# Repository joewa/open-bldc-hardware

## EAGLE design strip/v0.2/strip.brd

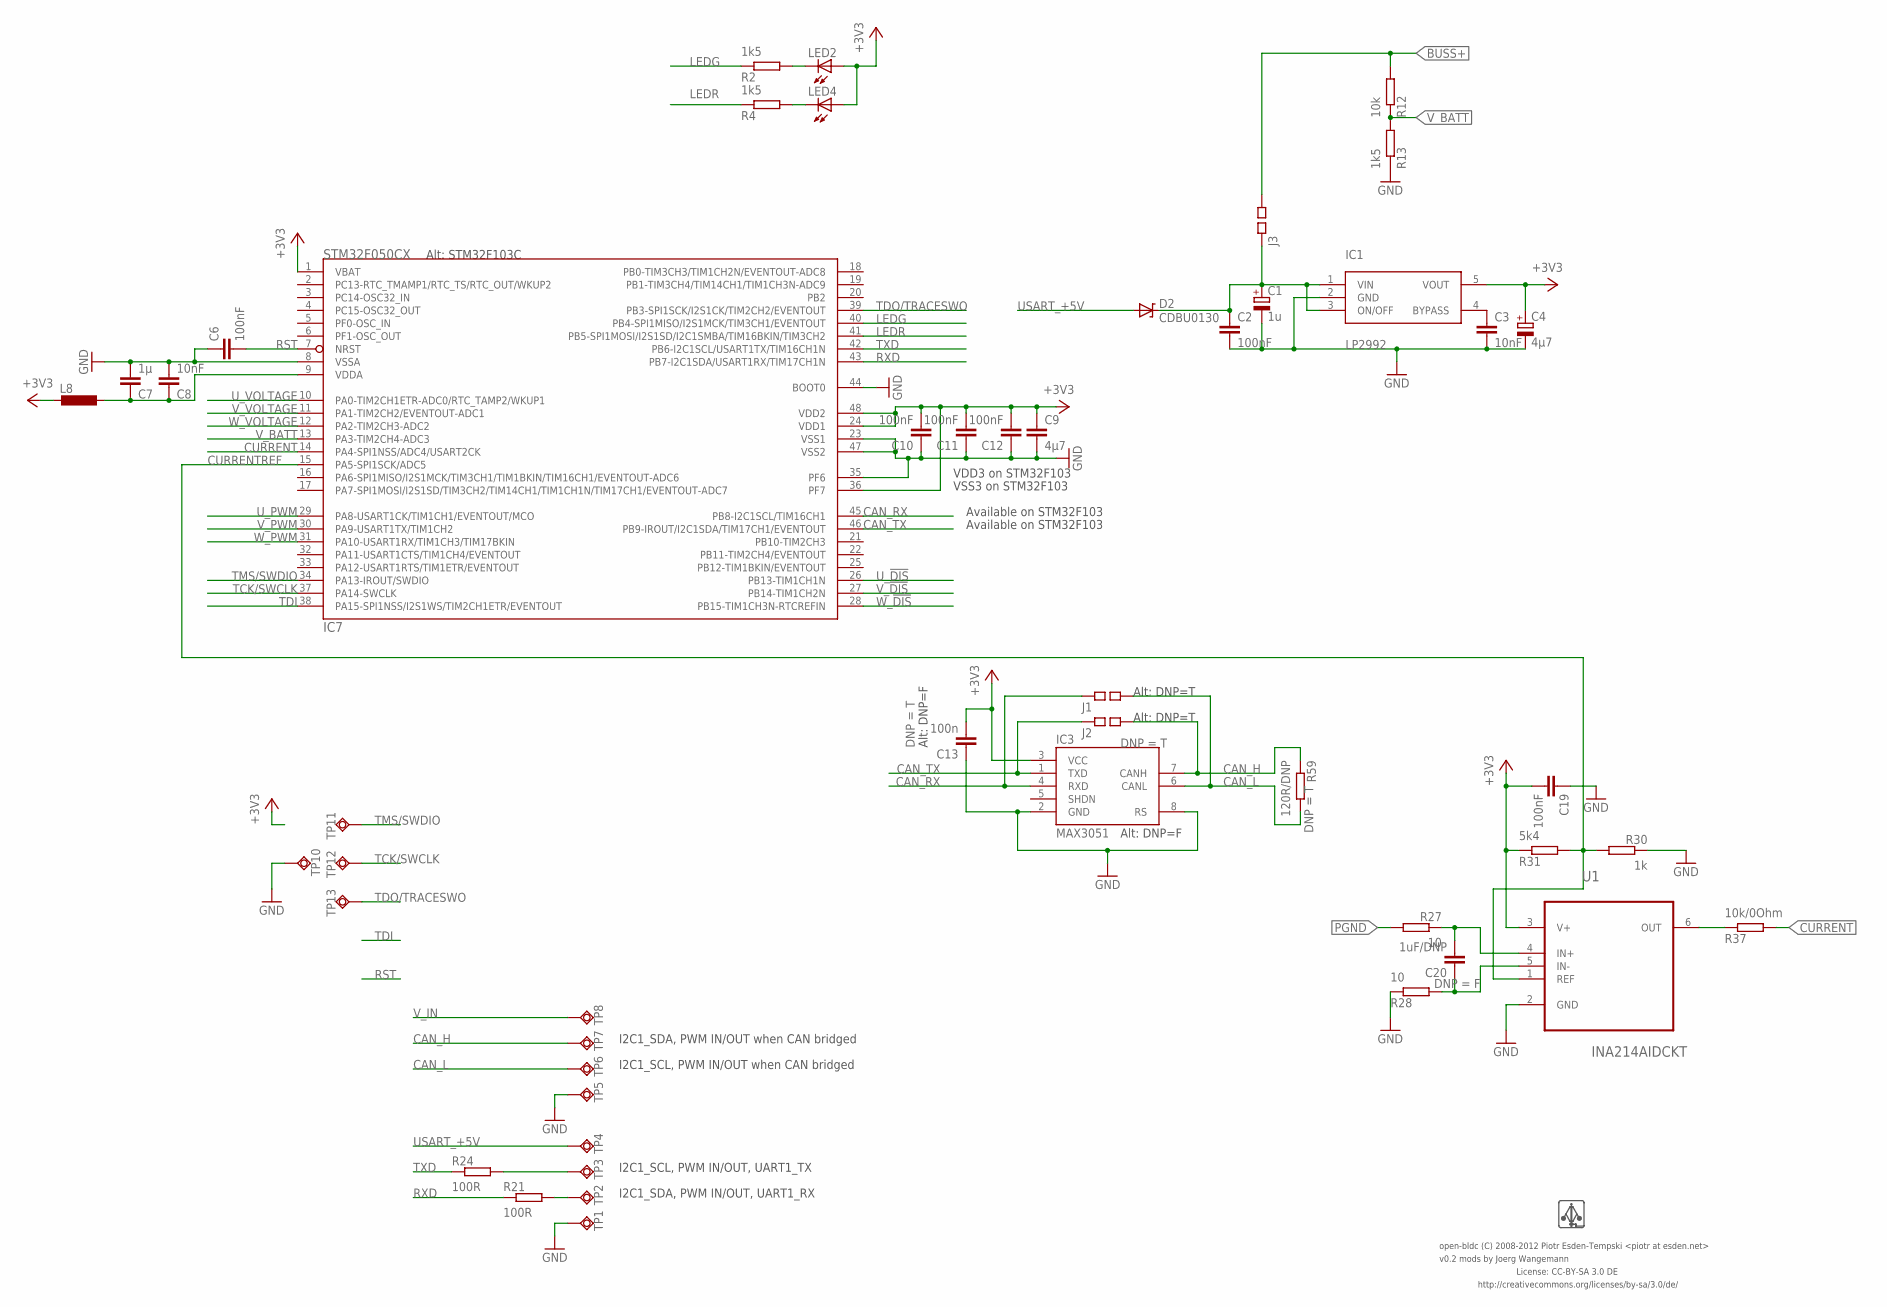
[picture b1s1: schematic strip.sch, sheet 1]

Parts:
C1: 1u; 0805-POL-CAP; PARTNO cap-cer-0805-1u-35v
C2, C6, C10, C11, C12, C19: 100nF; 0402-CAP; PARTNO cap-cer-0402-100n
C3, C8: 10nF; 0402-CAP; PARTNO cap-cer-0402-10n
C4: 4µ7; 0805-POL-CAP; PARTNO cap-cer-0805-4u7-16v
C7: 1µ; 0402-CAP; PARTNO cap-cer-0402-1u
C9: 4µ7; 0805-CAP; PARTNO cap-cer-0805-4u7
C13: 100n; 0402-CAP; PARTNO cap-cer-0402-100n
C20: 1uF/DNP; 0603-CAP; PARTNO cap-cer-0402-100n
D2: CDBU0130; 0603-DIO; PARTNO diode-0603
IC1: LP2992; SOT23-5; PARTNO vreg-sot-23-5-3v3
IC3: MAX3051; SO8; PARTNO *
IC7: STM32F050CX; LQFP48; PARTNO mcu-tqfp-32-stm32f05
J1, J2, J3: SQ_JMP-0402; 0402-SQJMP; PARTNO res-0402-0
L8: INDUCTOR-0603; 0603-IND; PARTNO ferrite-0603-600ohm
LED2: GREEN; 0402-LED; PARTNO led-0402-green
LED4: RED; 0402-LED; PARTNO led-0402-green
R2, R4, R13: 1k5; 0402-RES; PARTNO res-0402-1k5
R12: 10k; 0402-RES; PARTNO res-0402-10k
R21, R24: 100R; 0402-RES; PARTNO res-0402-100
R27: 10; 0402-RES; PARTNO res-0402-665
R28: 10; 0402-RES; PARTNO res-0402-560
R30: 1k; 0402-RES; PARTNO res-0402-1k
R31: 5k4; 0402-RES; PARTNO res-0402-5k36
R37: 10k/0Ohm; 0402-RES; PARTNO res-0402-0
R59: 120R/DNP; 0402-RES; PARTNO res-0402-60.4
TP1, TP2, TP3, TP4, TP5, TP6, TP7, TP8: TPSQTP20SQ; TP20SQ; PARTNO *
TP10, TP11, TP12, TP13: TPSQTP11SQ; TP11SQ; PARTNO *
U1: INA214AIDCKT; SOT65P210X110-6N
U$1: LOGO; LOGO_SILK_SMALL; PARTNO *

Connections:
+3V3: C4.+, C9.P$1 (1), C10.P$2 (2), C11.P$2 (2), C12.P$2 (2), C13.P$2 (2), C19.P$2 (2), IC1.5 (VOUT), IC3.3 (VCC), IC7.1 (VBAT), IC7.24 (VDD1), IC7.36 (PF7), IC7.48 (VDD2), L8.P$2 (2), LED2.A, LED4.A, R31.P$1 (1), U1.3 (V+)
BUSS+: J3.P$2 (2), R12.P$2 (2); also elsewhere on the board
CAN_H: IC3.7 (CANH), J2.P$2 (2), R59.P$1 (1), TP7.TP
CAN_L: IC3.6 (CANL), J1.P$2 (2), R59.P$2 (2), TP6.TP
CAN_RX: IC3.4 (RXD), IC7.45 (PB8-I2C1SCL/TIM16CH1), J1.P$1 (1)
CAN_TX: IC3.1 (TXD), IC7.46 (PB9-IROUT/I2C1SDA/TIM17CH1/EVENTOUT), J2.P$1 (1)
CURRENT: IC7.14 (PA4-SPI1NSS/ADC4/USART2CK), R37.P$2 (2)
CURRENTREF: IC7.15 (PA5-SPI1SCK/ADC5), R30.P$2 (2), R31.P$2 (2), U1.1 (REF)
CURRENT_RAW: R37.P$1 (1), U1.6 (OUT)
GND: C1.-, C2.P$2 (2), C3.P$2 (2), C4.-, C6.P$1 (1), C7.P$2 (2), C8.P$2 (2), C9.P$2 (2), C10.P$1 (1), C11.P$1 (1), C12.P$1 (1), C13.P$1 (1), C19.P$1 (1), IC1.2 (GND), IC3.2 (GND), IC3.8 (RS), IC7.8 (VSSA), IC7.23 (VSS1), IC7.35 (PF6), IC7.44 (BOOT0), IC7.47 (VSS2), R13.P$1 (1), R28.P$1 (1), R30.P$1 (1), TP1.TP, TP5.TP, TP10.TP, U1.2 (GND); also elsewhere on the board
INA21_INN: C20.P$1 (1), R28.P$2 (2), U1.5 (IN-)
INA21_INP: C20.P$2 (2), R27.P$1 (1), U1.4 (IN+)
LEDG: IC7.40 (PB4-SPI1MISO/I2S1MCK/TIM3CH1/EVENTOUT), R2.P$1 (1)
LEDR: IC7.41 (PB5-SPI1MOSI/I2S1SD/I2C1SMBA/TIM16BKIN/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), R4.P$1 (1)
unnamed: LED4.C, R4.P$2 (2)
unnamed: R21.P$2 (2), TP2.TP
unnamed: LED2.C, R2.P$2 (2)
unnamed: R24.P$2 (2), TP3.TP
unnamed: C3.P$1 (1), IC1.4 (BYPASS)
PGND: R27.P$2 (2); also elsewhere on the board
RST: C6.P$2 (2), IC7.7 (NRST)
RXD: IC7.43 (PB7-I2C1SDA/USART1RX/TIM17CH1N), R21.P$1 (1)
TCK/SWCLK: IC7.37 (PA14-SWCLK), TP12.TP
TDI: IC7.38 (PA15-SPI1NSS/I2S1WS/TIM2CH1ETR/EVENTOUT)
TDO/TRACESWO: IC7.39 (PB3-SPI1SCK/I2S1CK/TIM2CH2/EVENTOUT), TP13.TP
TMS/SWDIO: IC7.34 (PA13-IROUT/SWDIO), TP11.TP
TXD: IC7.42 (PB6-I2C1SCL/USART1TX/TIM16CH1N), R24.P$1 (1)
USART_+5V: D2.A, TP4.TP
U_!DIS: IC7.26 (PB13-TIM1CH1N); also elsewhere on the board
U_PWM: IC7.29 (PA8-USART1CK/TIM1CH1/EVENTOUT/MCO); also elsewhere on the board
U_VOLTAGE: IC7.10 (PA0-TIM2CH1ETR-ADC0/RTC_TAMP2/WKUP1); also elsewhere on the board
VDDA: C7.P$1 (1), C8.P$1 (1), IC7.9 (VDDA), L8.P$1 (1)
V_!DIS: IC7.27 (PB14-TIM1CH2N); also elsewhere on the board
V_BATT: IC7.13 (PA3-TIM2CH4-ADC3), R12.P$1 (1), R13.P$2 (2)
V_IN: C1.+, C2.P$1 (1), D2.C, IC1.1 (VIN), IC1.3 (ON/OFF), J3.P$1 (1), TP8.TP
V_PWM: IC7.30 (PA9-USART1TX/TIM1CH2); also elsewhere on the board
V_VOLTAGE: IC7.11 (PA1-TIM2CH2/EVENTOUT-ADC1); also elsewhere on the board
W_!DIS: IC7.28 (PB15-TIM1CH3N-RTCREFIN); also elsewhere on the board
W_PWM: IC7.31 (PA10-USART1RX/TIM1CH3/TIM17BKIN); also elsewhere on the board
W_VOLTAGE: IC7.12 (PA2-TIM2CH3-ADC2); also elsewhere on the board

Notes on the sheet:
License: CC-BY-SA 3.0 DE
http://creativecommons.org/licenses/by-sa/3.0/de/
open-bldc (C) 2008-2012 Piotr Esden-Tempski <piotr at esden.net>
VDD3 on STM32F103
VSS3 on STM32F103
Available on STM32F103
Alt: STM32F103C
Alt: DNP=T
Alt: DNP=F
I2C1_SDA, PWM IN/OUT when CAN bridged
I2C1_SCL, PWM IN/OUT when CAN bridged
I2C1_SCL, PWM IN/OUT, UART1_TX
I2C1_SDA, PWM IN/OUT, UART1_RX
v0.2 mods by Joerg Wangemann

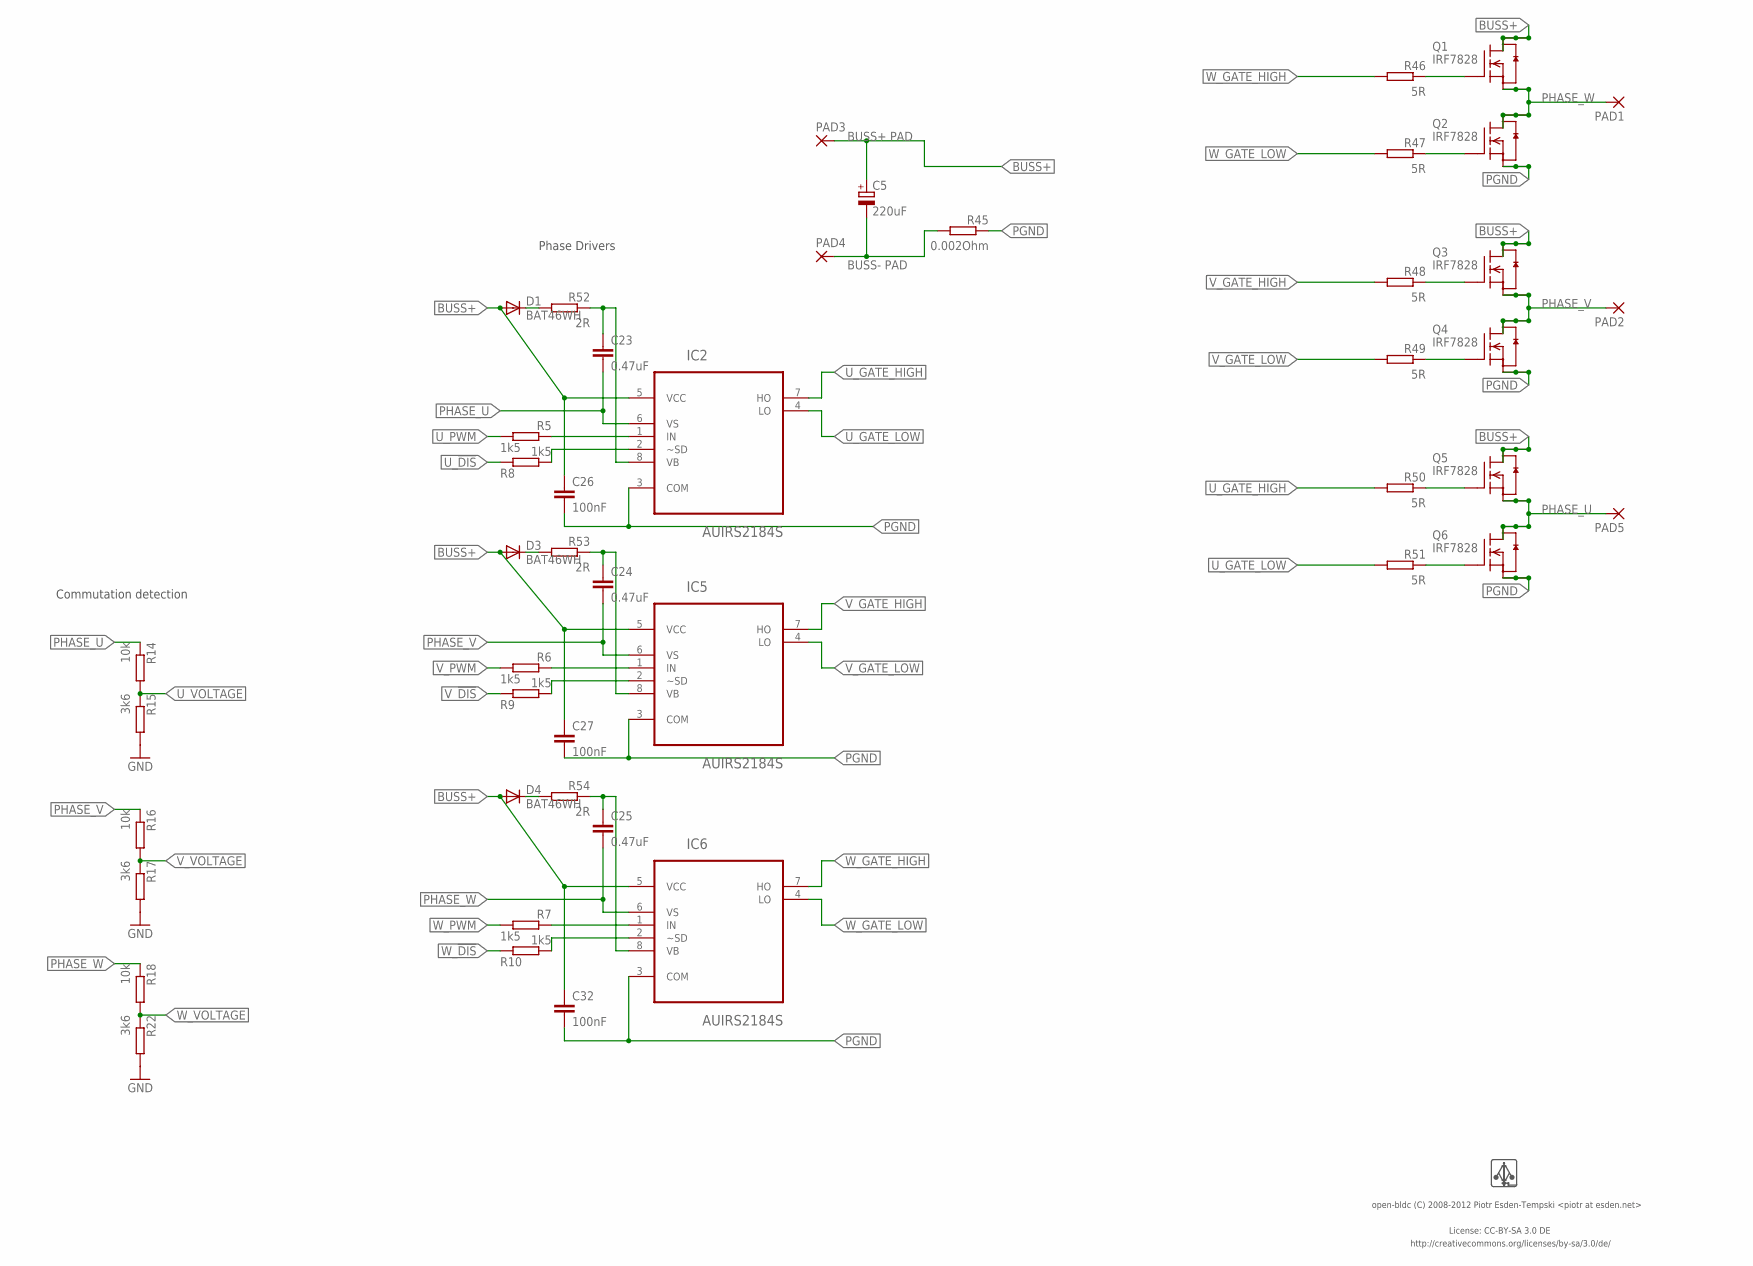
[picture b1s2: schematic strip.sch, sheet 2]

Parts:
C5: 220uF; 7343/D; PARTNO cap-tan-D-220u-16v
C23, C24, C25: 0.47uF; 0603-CAP; PARTNO cap-tan-0603-1u
C26, C27, C32: 100nF; 0603-CAP; PARTNO cap-cer-0402-100n
D1, D3, D4: BAT46WH; SOD-123-DIO; PARTNO *
IC2, IC5, IC6: AUIRS2184S; SOIC127P600X175-8N; PARTNO ic-so8-mosfet-driver-buck
PAD1, PAD2, PAD3, PAD4, PAD5: SMD5; SMD2,54-5,08; PARTNO *
Q1, Q2, Q3, Q4, Q5, Q6: IRF7828; SO8; PARTNO ic-so8-mosfet-n-ch-30v-15a
R5, R6, R7, R8, R9, R10: 1k5; 0402-RES; PARTNO res-0402-1k5
R14, R16, R18: 10k; 0402-RES; PARTNO res-0402-10k
R15, R17, R22: 3k6; 0402-RES; PARTNO *
R45: 0.002Ohm; 1206-RES; PARTNO res-1206-0005
R46, R47, R48, R49, R50, R51: 5R; 0603-RES; PARTNO res-0402-10
R52, R53, R54: 2R; 0402-RES; PARTNO res-0402-10
U$2: LOGO; LOGO_SILK_SMALL; PARTNO *

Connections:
BUSS+: C5.+, C26.P$1 (1), C27.P$1 (1), C32.P$1 (1), D1.A, D3.A, D4.A, IC2.5 (VCC), IC5.5 (VCC), IC6.5 (VCC), PAD3.1, Q1.5 (D1), Q1.6 (D2), Q1.7 (D3), Q1.8 (D4), Q3.5 (D1), Q3.6 (D2), Q3.7 (D3), Q3.8 (D4), Q5.5 (D1), Q5.6 (D2), Q5.7 (D3), Q5.8 (D4); also elsewhere on the board
GND: C5.-, PAD4.1, R15.P$2 (2), R17.P$2 (2), R22.P$2 (2), R45.P$2 (2); also elsewhere on the board
unnamed: D1.C, R52.P$2 (2)
unnamed: D4.C, R54.P$2 (2)
unnamed: D3.C, R53.P$2 (2)
PGND: C26.P$2 (2), C27.P$2 (2), C32.P$2 (2), IC2.3 (COM), IC5.3 (COM), IC6.3 (COM), Q2.1 (S3), Q2.2 (S2), Q2.3 (S1), Q4.1 (S3), Q4.2 (S2), Q4.3 (S1), Q6.1 (S3), Q6.2 (S2), Q6.3 (S1), R45.P$1 (1); also elsewhere on the board
PHASE_U: C23.P$2 (2), IC2.6 (VS), PAD5.1, Q5.1 (S3), Q5.2 (S2), Q5.3 (S1), Q6.5 (D1), Q6.6 (D2), Q6.7 (D3), Q6.8 (D4), R14.P$1 (1)
PHASE_V: C24.P$2 (2), IC5.6 (VS), PAD2.1, Q3.1 (S3), Q3.2 (S2), Q3.3 (S1), Q4.5 (D1), Q4.6 (D2), Q4.7 (D3), Q4.8 (D4), R16.P$1 (1)
PHASE_W: C25.P$2 (2), IC6.6 (VS), PAD1.1, Q1.1 (S3), Q1.2 (S2), Q1.3 (S1), Q2.5 (D1), Q2.6 (D2), Q2.7 (D3), Q2.8 (D4), R18.P$1 (1)
U_!DIS: R8.P$1 (1); also elsewhere on the board
U_GATE_HIGH: IC2.7 (HO), R50.P$2 (2)
U_GATE_HIGH_T: Q5.4 (G), R50.P$1 (1)
U_GATE_LOW: IC2.4 (LO), R51.P$2 (2)
U_GATE_LOW_T: Q6.4 (G), R51.P$1 (1)
U_PWM: R5.P$2 (2); also elsewhere on the board
U_PWM_IN: IC2.1 (IN), R5.P$1 (1)
U_SD: IC2.2 (~SD), R8.P$2 (2)
U_VB: C23.P$1 (1), IC2.8 (VB), R52.P$1 (1)
U_VOLTAGE: R14.P$2 (2), R15.P$1 (1); also elsewhere on the board
V_!DIS: R9.P$1 (1); also elsewhere on the board
V_GATE_HIGH: IC5.7 (HO), R48.P$2 (2)
V_GATE_HIGH_T: Q3.4 (G), R48.P$1 (1)
V_GATE_LOW: IC5.4 (LO), R49.P$2 (2)
V_GATE_LOW_T: Q4.4 (G), R49.P$1 (1)
V_PWM: R6.P$2 (2); also elsewhere on the board
V_PWM_IN: IC5.1 (IN), R6.P$1 (1)
V_SD: IC5.2 (~SD), R9.P$2 (2)
V_VB: C24.P$1 (1), IC5.8 (VB), R53.P$1 (1)
V_VOLTAGE: R16.P$2 (2), R17.P$1 (1); also elsewhere on the board
W_!DIS: R10.P$1 (1); also elsewhere on the board
W_GATE_HIGH: IC6.7 (HO), R46.P$2 (2)
W_GATE_HIGH_T: Q1.4 (G), R46.P$1 (1)
W_GATE_LOW: IC6.4 (LO), R47.P$2 (2)
W_GATE_LOW_T: Q2.4 (G), R47.P$1 (1)
W_PWM: R7.P$2 (2); also elsewhere on the board
W_PWM_IN: IC6.1 (IN), R7.P$1 (1)
W_SD: IC6.2 (~SD), R10.P$2 (2)
W_VB: C25.P$1 (1), IC6.8 (VB), R54.P$1 (1)
W_VOLTAGE: R18.P$2 (2), R22.P$1 (1); also elsewhere on the board

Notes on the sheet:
Phase Drivers
Commutation detection
BUSS+ PAD
BUSS- PAD
License: CC-BY-SA 3.0 DE
http://creativecommons.org/licenses/by-sa/3.0/de/
open-bldc (C) 2008-2012 Piotr Esden-Tempski <piotr at esden.net>

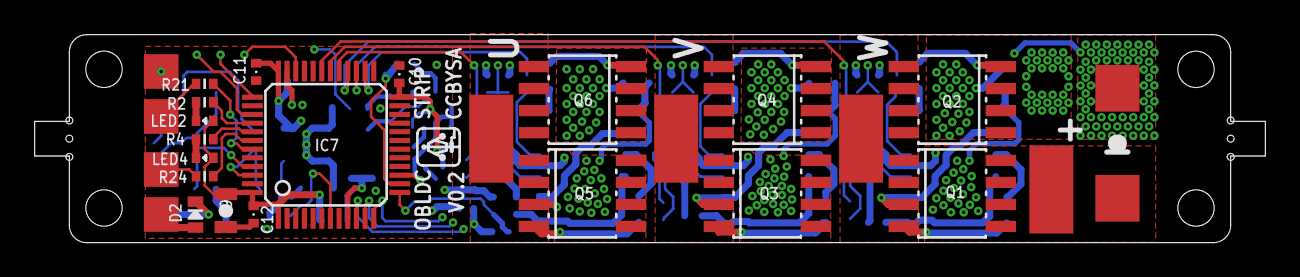
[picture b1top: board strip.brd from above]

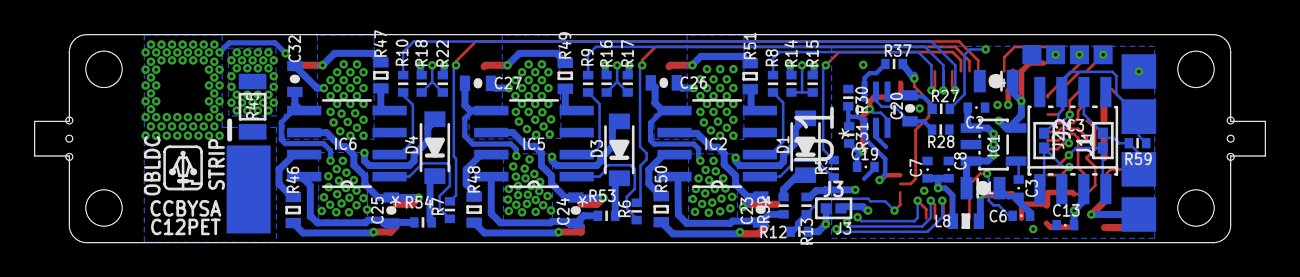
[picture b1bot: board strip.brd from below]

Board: 4 copper layers, 71.0 x 12.0 mm, 97 parts (69 on the bottom side), 66 nets.

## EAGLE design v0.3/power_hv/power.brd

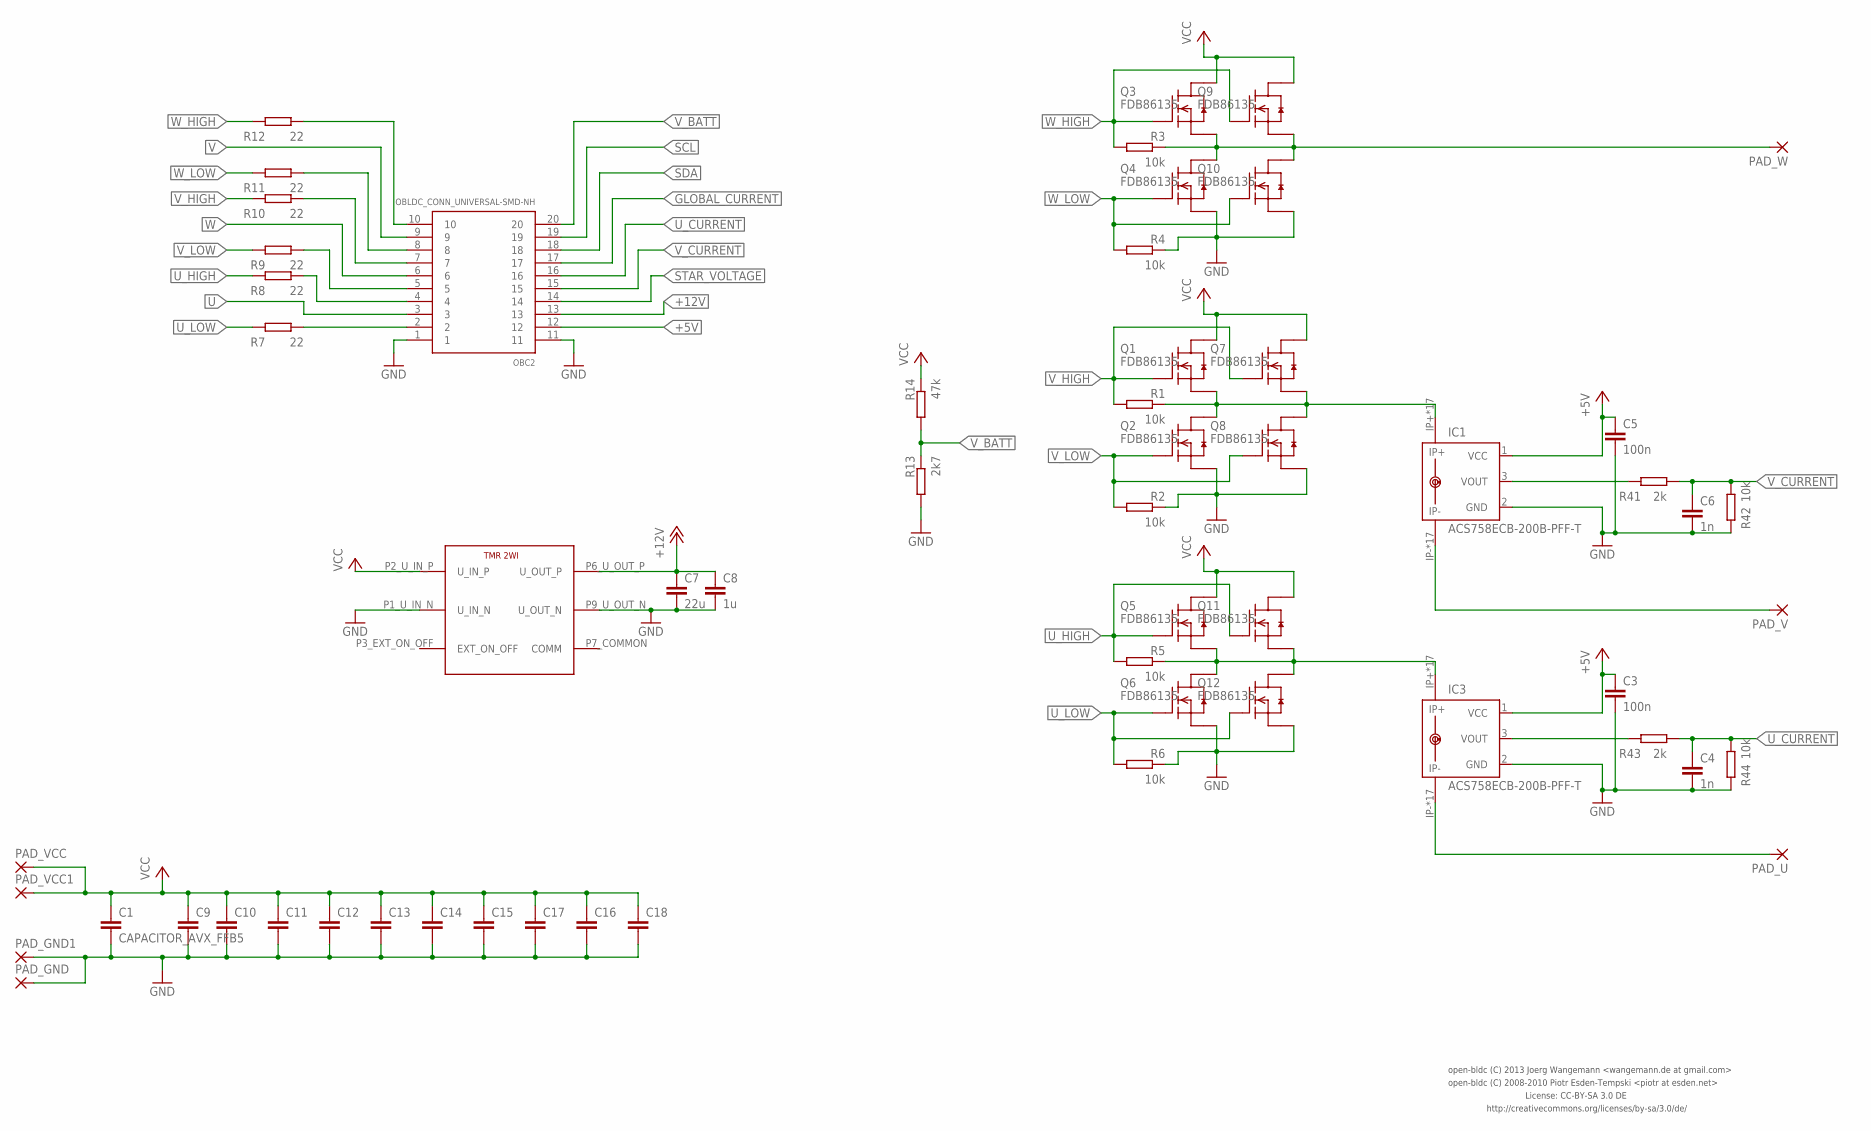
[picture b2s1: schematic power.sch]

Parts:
C1: CAPACITOR_AVX_FFB5; AVX_FFB5
C3, C5: 100n; 0603-CAP
C4, C6: 1n; 0603-CAP
C7: 22u; C2220K
C8: 1u; C1206
C9, C10, C11, C12, C13, C14, C15, C16, C17, C18: C-EUC2220K; C2220K
IC1, IC3: ACS758ECB-200B-PFF-T; CB-PFF
OBC2: OBLDC_CONN_UNIVERSAL-SMD-NH; OBLDC_CONN_SMD_NO_HOLES
PAD_GND, PAD_GND1: WIREPAD-2MM; WIREPAD_2MM
PAD_U: WIREPAD-2MM; WIREPAD_2MM
PAD_V: WIREPAD-2MM; WIREPAD_2MM
PAD_VCC, PAD_VCC1: WIREPAD-2MM; WIREPAD_2MM
PAD_W: WIREPAD-2MM; WIREPAD_2MM
Q1, Q2, Q3, Q4, Q5, Q6, Q7, Q8, Q9, Q10, Q11, Q12: FDB86135; DPAK
R1, R2, R3, R4, R5, R6: 10k; 0603-SF-RES
R7, R8, R9, R10, R11, R12: 22; 1206-RES
R13: 2k7; 1206-RES
R14: 47k; 1206-RES
R41, R43: 2k; 0603-RES
R42, R44: 10k; 0603-RES
U$2: TRACO_TMR_2WI

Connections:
+5V: C3.P$1 (1), C5.P$1 (1), IC1.1 (VCC), IC3.1 (VCC), OBC2.12
+12V: C7.1, C8.1, OBC2.13, U$2.P6_U_OUT_P (U_OUT_P)
GLOBAL_CURRENT: OBC2.17
GND: C1.P$2 (2), C3.P$2 (2), C4.P$2 (2), C5.P$2 (2), C6.P$2 (2), C7.2, C8.2, C9.2, C10.2, C11.2, C12.2, C13.2, C14.2, C15.2, C16.2, C17.2, C18.2, IC1.2 (GND), IC3.2 (GND), OBC2.1, OBC2.11, PAD_GND.1, PAD_GND1.1, Q2.3 (S), Q4.3 (S), Q6.3 (S), Q8.3 (S), Q10.3 (S), Q12.3 (S), R2.1, R4.1, R6.1, R13.P$2 (2), R42.P$2 (2), R44.P$2 (2), U$2.P1_U_IN_N (U_IN_N), U$2.P9_U_OUT_N (U_OUT_N)
unnamed: IC1.3 (VOUT), R41.P$2 (2)
unnamed: OBC2.2, R7.P$1 (1)
unnamed: OBC2.4, R8.P$1 (1)
unnamed: OBC2.5, R9.P$1 (1)
unnamed: OBC2.7, R10.P$1 (1)
unnamed: OBC2.8, R11.P$1 (1)
unnamed: OBC2.10, R12.P$1 (1)
unnamed: IC3.3 (VOUT), R43.P$2 (2)
SCL: OBC2.19
SDA: OBC2.18
STAR_VOLTAGE: OBC2.14
U: IC3.IP+, IC3.IP+@2 (IP+), IC3.IP+@3 (IP+), IC3.IP+@4 (IP+), IC3.IP+@5 (IP+), IC3.IP+@6 (IP+), IC3.IP+@7 (IP+), IC3.IP+@8 (IP+), IC3.IP+@9 (IP+), IC3.IP+@10 (IP+), IC3.IP+@11 (IP+), IC3.IP+@12 (IP+), IC3.IP+@13 (IP+), IC3.IP+@14 (IP+), IC3.IP+@15 (IP+), IC3.IP+@16 (IP+), IC3.IP+@17 (IP+), OBC2.3, Q5.3 (S), Q6.P$1 (D), Q11.3 (S), Q12.P$1 (D), R5.1
U_CURRENT: C4.P$1 (1), OBC2.16, R43.P$1 (1), R44.P$1 (1)
U_HIGH: Q5.1 (G), Q11.1 (G), R5.2, R8.P$2 (2)
U_LOW: Q6.1 (G), Q12.1 (G), R6.2, R7.P$2 (2)
U_PAD: IC3.IP-, IC3.IP-@2 (IP-), IC3.IP-@3 (IP-), IC3.IP-@4 (IP-), IC3.IP-@5 (IP-), IC3.IP-@6 (IP-), IC3.IP-@7 (IP-), IC3.IP-@8 (IP-), IC3.IP-@9 (IP-), IC3.IP-@10 (IP-), IC3.IP-@11 (IP-), IC3.IP-@12 (IP-), IC3.IP-@13 (IP-), IC3.IP-@14 (IP-), IC3.IP-@15 (IP-), IC3.IP-@16 (IP-), IC3.IP-@17 (IP-), PAD_U.1
V: IC1.IP+, IC1.IP+@2 (IP+), IC1.IP+@3 (IP+), IC1.IP+@4 (IP+), IC1.IP+@5 (IP+), IC1.IP+@6 (IP+), IC1.IP+@7 (IP+), IC1.IP+@8 (IP+), IC1.IP+@9 (IP+), IC1.IP+@10 (IP+), IC1.IP+@11 (IP+), IC1.IP+@12 (IP+), IC1.IP+@13 (IP+), IC1.IP+@14 (IP+), IC1.IP+@15 (IP+), IC1.IP+@16 (IP+), IC1.IP+@17 (IP+), OBC2.9, Q1.3 (S), Q2.P$1 (D), Q7.3 (S), Q8.P$1 (D), R1.1
VCC: C1.P$1 (1), C9.1, C10.1, C11.1, C12.1, C13.1, C14.1, C15.1, C16.1, C17.1, C18.1, PAD_VCC.1, PAD_VCC1.1, Q1.P$1 (D), Q3.P$1 (D), Q5.P$1 (D), Q7.P$1 (D), Q9.P$1 (D), Q11.P$1 (D), R14.P$1 (1), U$2.P2_U_IN_P (U_IN_P)
V_BATT: OBC2.20, R13.P$1 (1), R14.P$2 (2)
V_CURRENT: C6.P$1 (1), OBC2.15, R41.P$1 (1), R42.P$1 (1)
V_HIGH: Q3.1 (G), Q9.1 (G), R3.2, R10.P$2 (2)
V_LOW: Q4.1 (G), Q10.1 (G), R4.2, R9.P$2 (2)
V_PAD: IC1.IP-, IC1.IP-@2 (IP-), IC1.IP-@3 (IP-), IC1.IP-@4 (IP-), IC1.IP-@5 (IP-), IC1.IP-@6 (IP-), IC1.IP-@7 (IP-), IC1.IP-@8 (IP-), IC1.IP-@9 (IP-), IC1.IP-@10 (IP-), IC1.IP-@11 (IP-), IC1.IP-@12 (IP-), IC1.IP-@13 (IP-), IC1.IP-@14 (IP-), IC1.IP-@15 (IP-), IC1.IP-@16 (IP-), IC1.IP-@17 (IP-), PAD_V.1
W: OBC2.6, PAD_W.1, Q3.3 (S), Q4.P$1 (D), Q9.3 (S), Q10.P$1 (D), R3.1
W_HIGH: Q1.1 (G), Q7.1 (G), R1.2, R12.P$2 (2)
W_LOW: Q2.1 (G), Q8.1 (G), R2.2, R11.P$2 (2)

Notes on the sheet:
License: CC-BY-SA 3.0 DE
http://creativecommons.org/licenses/by-sa/3.0/de/
open-bldc (C) 2008-2010 Piotr Esden-Tempski <piotr at esden.net>
open-bldc (C) 2013 Joerg Wangemann <wangemann.de at gmail.com>

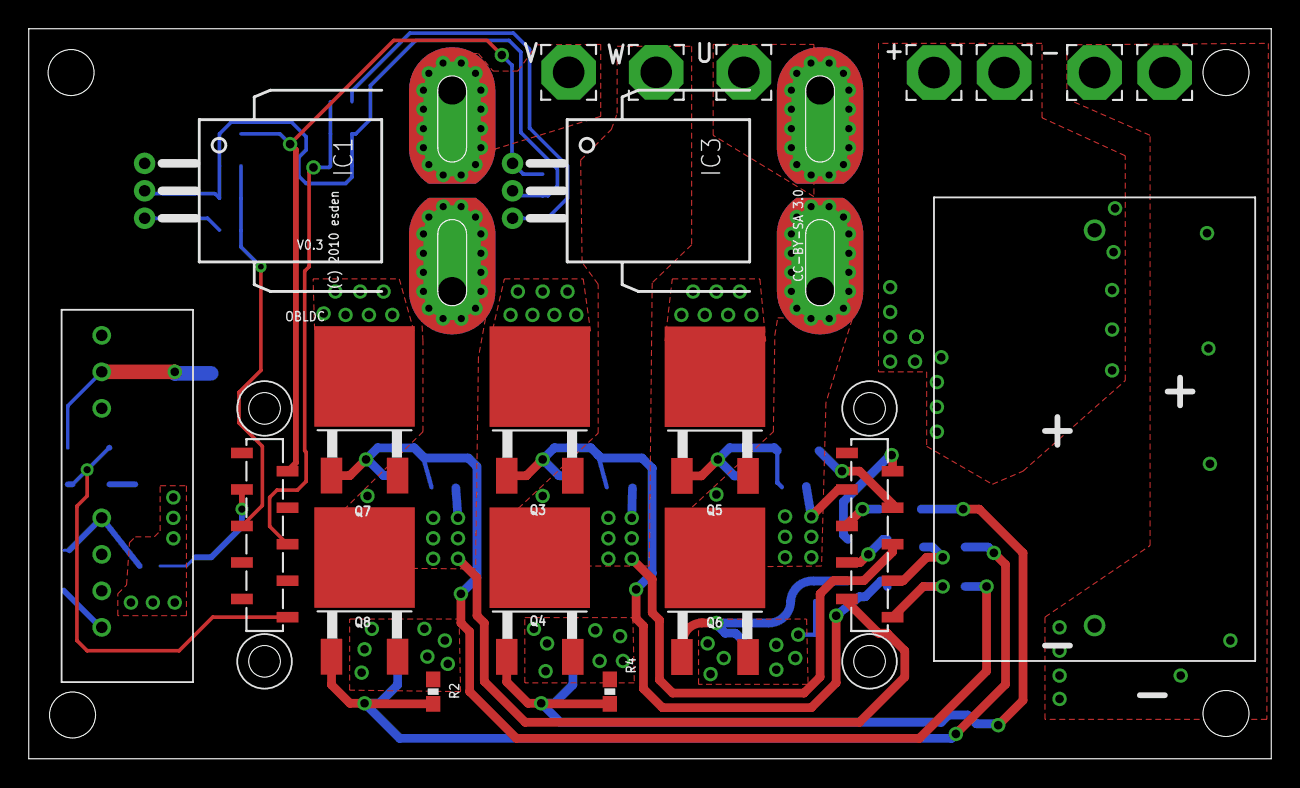
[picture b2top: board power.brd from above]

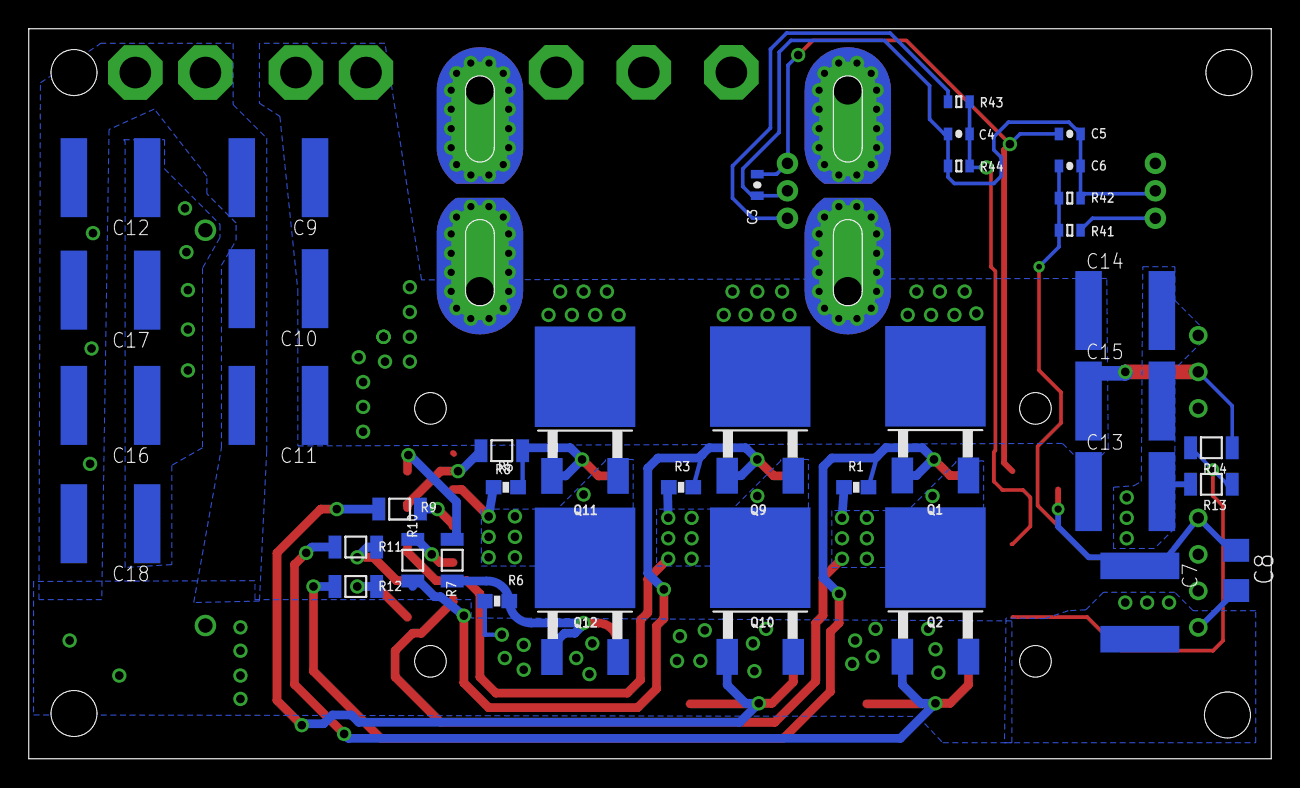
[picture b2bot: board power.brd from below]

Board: 4 copper layers, 86.5 x 50.8 mm, 59 parts (38 on the bottom side), 26 nets.

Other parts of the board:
U$1: OBLDC_MECH

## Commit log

2013-10-06 Added the new high voltage power board.
2013-10-07 TODO: Route ground connection to driver board.
2013-10-12 Added some notes on the power stage power_hv v.0.3.
2013-10-22 Added new variant of the strip board.
2013-10-23 Updated bootstrap circuit.
2013-10-23 Updated bootstrap circuit
2013-10-24 Updated current measurement circuit.
2013-10-25 Wired the layout of the new current measurement.
2013-10-29 Fixed some part descriptons.
2013-11-08 Strip v0.2 layout after manufacturer review.
2013-11-28 Corrected some component values.
2014-05-27 Pin COM of the IRS2184 driver is now connected to PGND... as it should.
2015-04-05 Addded some pictures of the board.

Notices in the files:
v0.3/power_hv/power.brd:
(C) 2010 esden
